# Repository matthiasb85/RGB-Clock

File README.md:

RGB-Clock
=========

RGB-Clock with STM32F1, DCF77, ESP8266, IR RC5 and LDR.

The following features are implemented (1-3) or will be implemented later (4-7)

1.) Fast STM32F103 @72MHz

2.) WS2812B RGB stripe, controlled via PWM & DMA (~0% CPU usage)

3.) DCF77 receiver for time snych

4.) ESP8266 Wifi module for HTTP interface and NTP time synch

5.) IR RC5 receiver integration

6.) Ambient dependent lighting with LDR

7.) MicroSD Card as storage device

The board uses a standard ARM JTAG interface. In addition all remaining GPIOs and the ESP8266 are available on an external pinheader.

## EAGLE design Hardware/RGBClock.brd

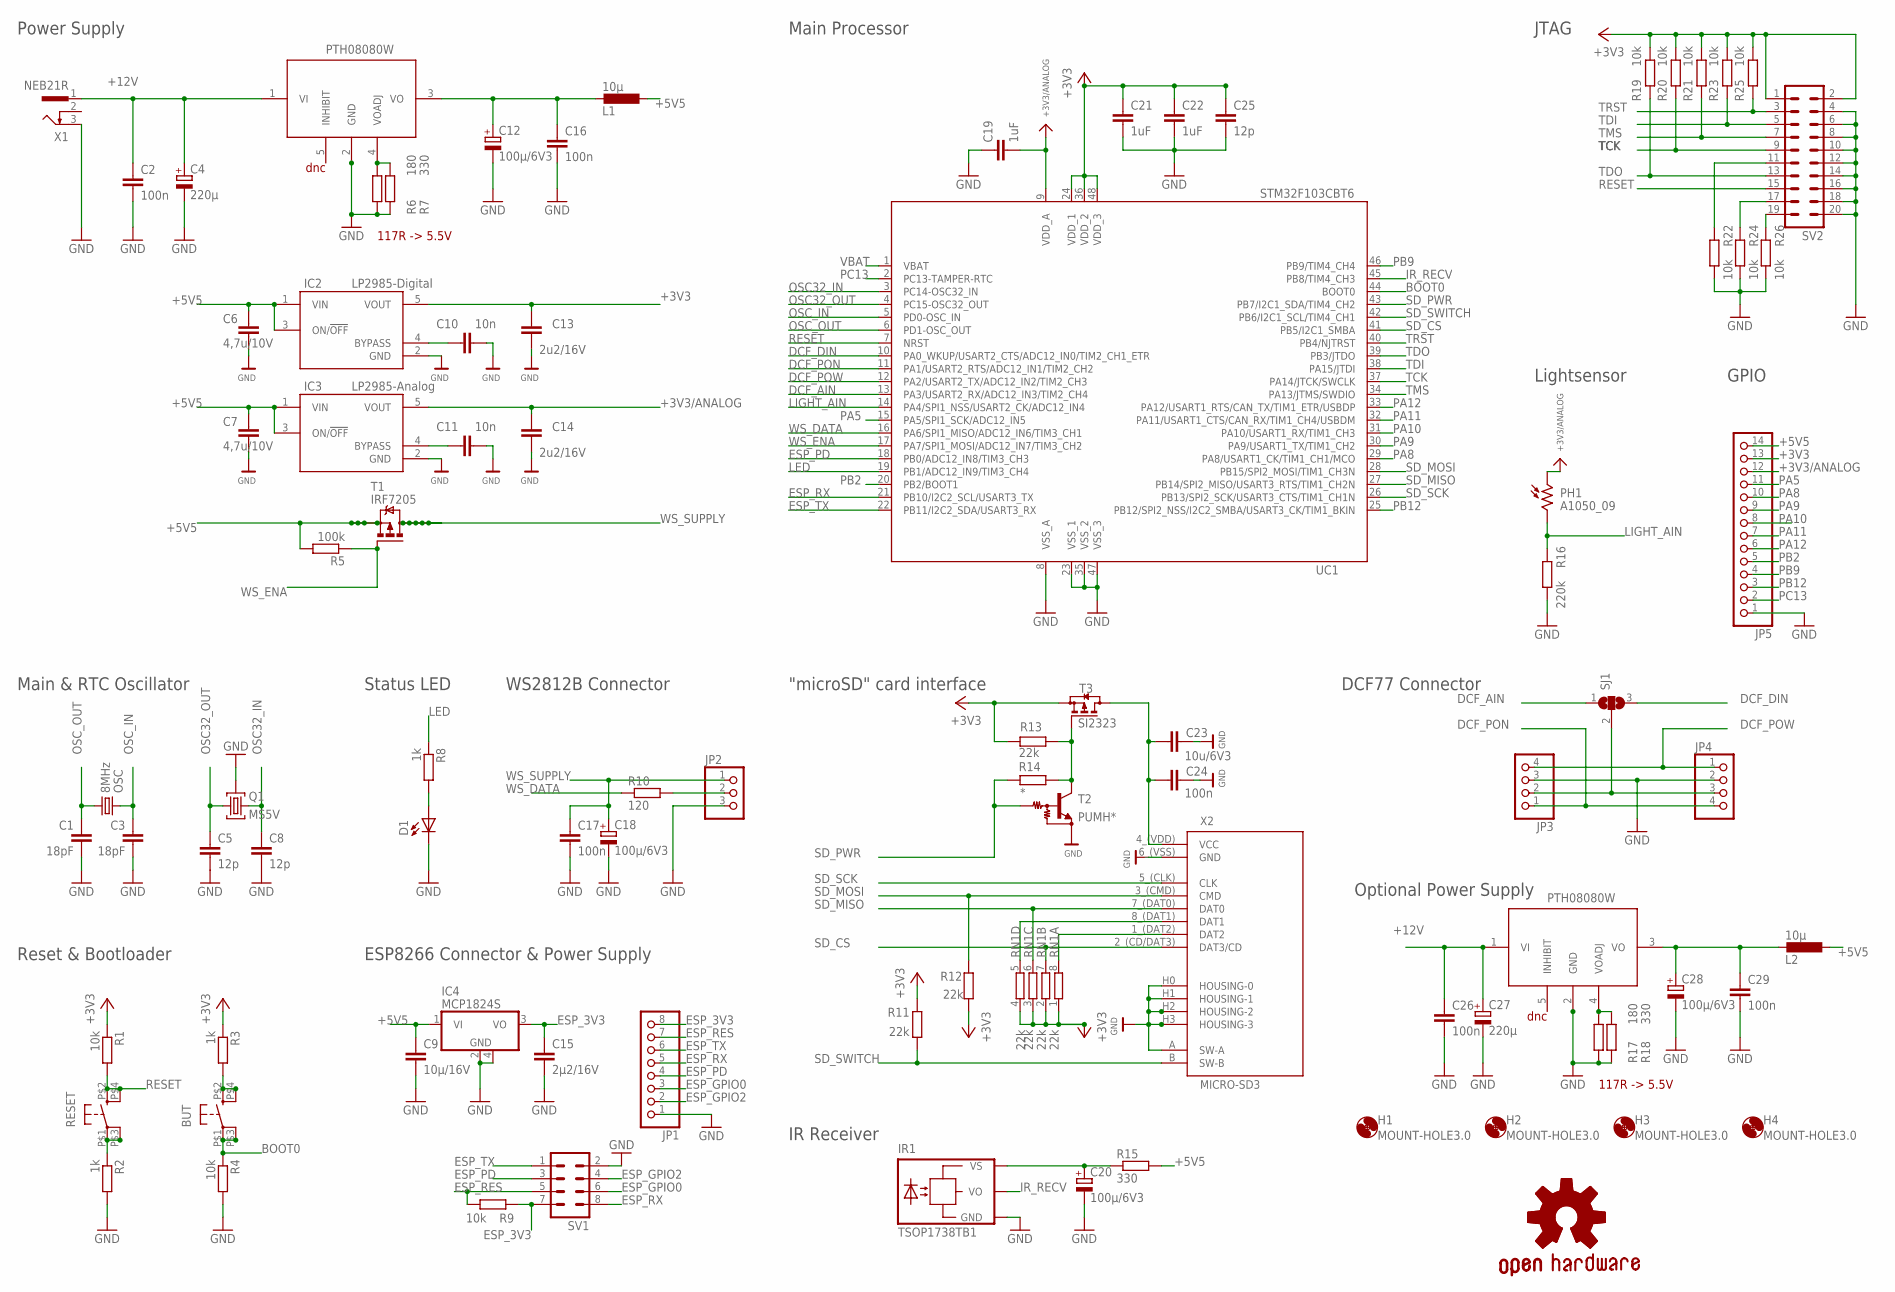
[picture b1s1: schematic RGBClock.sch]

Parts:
BUT: KMR211GLFS; PUSHBUTTON-KMR241GLFS
C1, C3: 18pF; C0402
C2, C16, C17, C26, C29: 100n; C0603
C4, C27: 220µ; E3,5-8
C5, C8, C25: 12p; C0603
C6, C7: 4,7u/10V; C0603-DASHES
C9: 10µ/16V; C0805
C10, C11: 10n; C0603-DASHES
C12, C18, C20, C28: 100µ/6V3; PANASONIC_C
C13, C14: 2u2/16V; C0603-DASHES
C15: 2µ2/16V; C0603
C19, C21, C22: 1uF; C0603
C23: 10u/6V3; C0603-DASHES
C24: 100n; C0603-DASHES
D1: Blue; LED-1206
GOLD_ORB_SM1: OSHWLOGO_GOLD_ORB_MED; OSHW1
H1, H2, H3, H4: MOUNT-HOLE3.0; 3,0
IC1, IC5: PTH08080W
IC2: LP2985-Digital; SOT23-5
IC3: LP2985-Analog; SOT23-5
IC4: MCP1824S; SOT223
IR1: TSOP1738TB1; TSOP17_TB1
JP1: PINHD-1X8/90; 1X08/90
JP2: PINHD-1X3/90; 1X03/90
JP3, JP4: PINHD-1X4; 1X04
JP5: PINHD-1X14/90; 1X14/90
L1, L2: 10µ; SD53-XXX-R; DIGIKEY-PN 513-1457-1-ND
OSC: 8MHz; CRYSTAL-SMD-5X3
PH1: A1050_09; T0-46-A10XX
Q1: MS5V
R1, R4, R9, R19, R20, R21, R22, R23, R24, R25, R26: 10k; R0603
R2, R3, R8: 1k; R0603
R5: 100k; R0603
R6, R17: 180; R0603
R7, R15, R18: 330; R0603
R10: 120; R0603
R11, R12, R13: 22k; R0603-DASHES
R14: *; R0603-DASHES
R16: 220k; R0603
RESET: KMR211GLFS; PUSHBUTTON-KMR241GLFS
RN1: 22k; CRA3A4E; PART_TYPE EXB-N8V
SJ1: SJ2W0603; JUM0603
SV1: MA04-2
SV2: ML20L
T1: IRF7205; SO-08
T2: PUMH*; SOT23
T3: SI2323; SOT23
UC1: STM32F103CBT6; LQFP48
X1: NEB21R
X2: MICRO-SD3; HIROSE_DM3AT

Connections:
+3V3: C13.1, C21.1, C22.1, C25.1, IC2.5 (VOUT), JP5.13, R1.1, R3.1, R11.2, R12.2, R13.2, R19.1, R20.1, R21.1, R23.1, R25.1, RN1.1, RN1.2 (1), RN1.3 (1), RN1.4 (1), SV2.1, SV2.2, T3.2 (S), UC1.24 (VDD_1), UC1.36 (VDD_2), UC1.48 (VDD_3)
+3V3/ANALOG: C14.1, C19.2, IC3.5 (VOUT), JP5.12, PH1.1, UC1.9 (VDD_A)
+5V5: C6.1, C7.1, C9.1, IC2.1 (VIN), IC2.3 (ON/!OFF), IC3.1 (VIN), IC3.3 (ON/!OFF), IC4.1 (VI), JP5.14, L1.1, L2.1, R5.2, R15.2, T1.1 (S), T1.2 (S), T1.3 (S)
+6V_EXT: C12.+, C16.1, IC1.3 (VO), L1.2
+6V_EXT1: C28.+, C29.1, IC5.3 (VO), L2.2
+12V: C2.1, C4.+, C26.1, C27.+, IC1.1 (VI), IC5.1 (VI), X1.1
BOOT0: BUT.P$1 (1), BUT.P$3 (3), R4.1, UC1.44 (BOOT0)
DCF_AIN: SJ1.1, UC1.13 (PA3/USART2_RX/ADC12_IN3/TIM2_CH4)
DCF_DIN: SJ1.3, UC1.10 (PA0_WKUP/USART2_CTS/ADC12_IN0/TIM2_CH1_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)
DCF_PON: JP3.1, JP4.4, UC1.11 (PA1/USART2_RTS/ADC12_IN1/TIM2_CH2)
DCF_POW: JP3.4, JP4.1, UC1.12 (PA2/USART2_TX/ADC12_IN2/TIM2_CH3)
ESP_3V3: C15.1, IC4.3 (VO), JP1.8, R9.2, SV1.7
ESP_GPIO0: JP1.3, SV1.6
ESP_GPIO2: JP1.2, SV1.4
ESP_PD: JP1.4, SV1.3, UC1.18 (PB0/ADC12_IN8/TIM3_CH3)
ESP_RES: JP1.7, R9.1, SV1.5
ESP_RX: JP1.5, SV1.8, UC1.21 (PB10/I2C2_SCL/USART3_TX)
ESP_TX: JP1.6, SV1.1, UC1.22 (PB11/I2C2_SDA/USART3_RX)
GND: C1.2, C2.2, C3.2, C4.-, C5.2, C6.2, C7.2, C8.2, C9.2, C10.2, C11.2, C12.-, C13.2, C14.2, C15.2, C16.2, C17.2, C18.-, C19.1, C20.-, C21.2, C22.2, C23.2, C24.2, C25.2, C26.2, C27.-, C28.-, C29.2, D1.C, IC1.2 (GND), IC2.2 (GND), IC3.2 (GND), IC4.2 (GND), IC4.4 (GND), IC5.2 (GND), IR1.GND, JP1.1, JP2.3, JP3.3, JP4.2, JP5.1, Q1.H (3), R2.2, R4.2, R6.2, R7.2, R16.1, R17.2, R18.2, R22.1, R24.1, R26.1, SV1.2, SV2.4, SV2.6, SV2.8, SV2.10, SV2.12, SV2.14, SV2.16, SV2.18, SV2.20, T2.2 (E), UC1.8 (VSS_A), UC1.23 (VSS_1), UC1.35 (VSS_2), UC1.47 (VSS_3), X1.3, X2.6_(VSS) (GND), X2.A (SW-A), X2.H0 (HOUSING-0), X2.H1 (HOUSING-1), X2.H2 (HOUSING-2), X2.H3 (HOUSING-3)
IR_RECV: IR1.VO, UC1.45 (PB8/TIM4_CH3)
LED: R8.1, UC1.19 (PB1/ADC12_IN9/TIM3_CH4)
LIGHT_AIN: PH1.2, R16.2, UC1.14 (PA4/SPI1_NSS/USART2_CK/ADC12_IN4)
LP2985_BYPASS: C11.1, IC3.4 (BYPASS)
LP2985_BYPASS1: C10.1, IC2.4 (BYPASS)
unnamed: BUT.P$2 (2), BUT.P$4 (4), R3.2
unnamed: D1.A, R8.2
unnamed: JP2.2, R10.2
unnamed: R2.1, RESET.P$1 (1), RESET.P$3 (3)
unnamed: IC5.4 (VOADJ), R17.1, R18.1
unnamed: R26.2, SV2.19
unnamed: JP3.2, JP4.3, SJ1.2
unnamed: R24.2, SV2.17
unnamed: R22.2, SV2.11
unnamed: C20.+, IR1.VS, R15.1
unnamed: RN1.8 (2), X2.1_(DAT2) (DAT2)
unnamed: RN1.5 (2), X2.8_(DAT1) (DAT1)
unnamed: IC1.4 (VOADJ), R6.1, R7.1
OSC32_IN: C8.1, Q1.2, UC1.3 (PC14-OSC32_IN)
OSC32_OUT: C5.1, Q1.1, UC1.4 (PC15-OSC32_OUT)
OSC_IN: C3.1, OSC.3 (2), UC1.5 (PD0-OSC_IN)
OSC_OUT: C1.1, OSC.1, UC1.6 (PD1-OSC_OUT)
PA5: JP5.11, UC1.15 (PA5/SPI1_SCK/ADC12_IN5)
PA8: JP5.10, UC1.29 (PA8/USART1_CK/TIM1_CH1/MCO)
PA9: JP5.9, UC1.30 (PA9/USART1_TX/TIM1_CH2)
PA10: JP5.8, UC1.31 (PA10/USART1_RX/TIM1_CH3)
PA11: JP5.7, UC1.32 (PA11/USART1_CTS/CAN_RX/TIM1_CH4/USBDM)
PA12: JP5.6, UC1.33 (PA12/USART1_RTS/CAN_TX/TIM1_ETR/USBDP)
PB2: JP5.5, UC1.20 (PB2/BOOT1)
PB9: JP5.4, UC1.46 (PB9/TIM4_CH4)
PB12: JP5.3, UC1.25 (PB12/SPI2_NSS/I2C2_SMBA/USART3_CK/TIM1_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)
PC13: JP5.2, UC1.2 (PC13-TAMPER-RTC)
RESET: R1.2, RESET.P$2 (2), RESET.P$4 (4), SV2.15, UC1.7 (NRST)
SDIO_VCC: C23.1, C24.1, T3.3 (D), X2.4_(VDD) (VCC)
SD_CS: RN1.7 (2), UC1.41 (PB5/I2C1_SMBA), X2.2_(CD/DAT3) (DAT3/CD)
SD_MISO: RN1.6 (2), UC1.27 (PB14/SPI2_MISO/USART3_RTS/TIM1_CH2N), X2.7_(DAT0) (DAT0)
SD_MOSI: R12.1, UC1.28 (PB15/SPI2_MOSI/TIM1_CH3N), X2.3_(CMD) (CMD)
SD_PWR: R14.2, T2.1 (B), UC1.43 (PB7/I2C1_SDA/TIM4_CH2)
SD_PWR_INV: R13.1, R14.1, T2.3 (C), T3.1 (G)
SD_SCK: UC1.26 (PB13/SPI2_SCK/USART3_CTS/TIM1_CH1N), X2.5_(CLK) (CLK)
SD_SWITCH: R11.1, UC1.42 (PB6/I2C1_SCL/TIM4_CH1), X2.B (SW-B)
TCK: R20.2, SV2.9, UC1.37 (PA14/JTCK/SWCLK)
TDI: R23.2, SV2.5, UC1.38 (PA15/JTDI)
TDO: R19.2, SV2.13, UC1.39 (PB3/JTDO)
TMS: R21.2, SV2.7, UC1.34 (PA13/JTMS/SWDIO)
TRST: R25.2, SV2.3, UC1.40 (PB4/NJTRST)
VBAT: UC1.1 (VBAT)
WS_DATA: R10.1, UC1.16 (PA6/SPI1_MISO/ADC12_IN6/TIM3_CH1)
WS_ENA: R5.1, T1.4 (G), UC1.17 (PA7/SPI1_MOSI/ADC12_IN7/TIM3_CH2)
WS_SUPPLY: C17.1, C18.+, JP2.1, T1.5 (D), T1.6 (D), T1.7 (D), T1.8 (D)

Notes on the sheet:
PTH08080W
117R -> 5.5V
dnc
"microSD" card interface
Power Supply
Main Processor
Main & RTC Oscillator
Reset & Bootloader
DCF77 Connector
Status LED
WS2812B Connector
IR Receiver
ESP8266 Connector & Power Supply
JTAG
Lightsensor
GPIO
Optional Power Supply

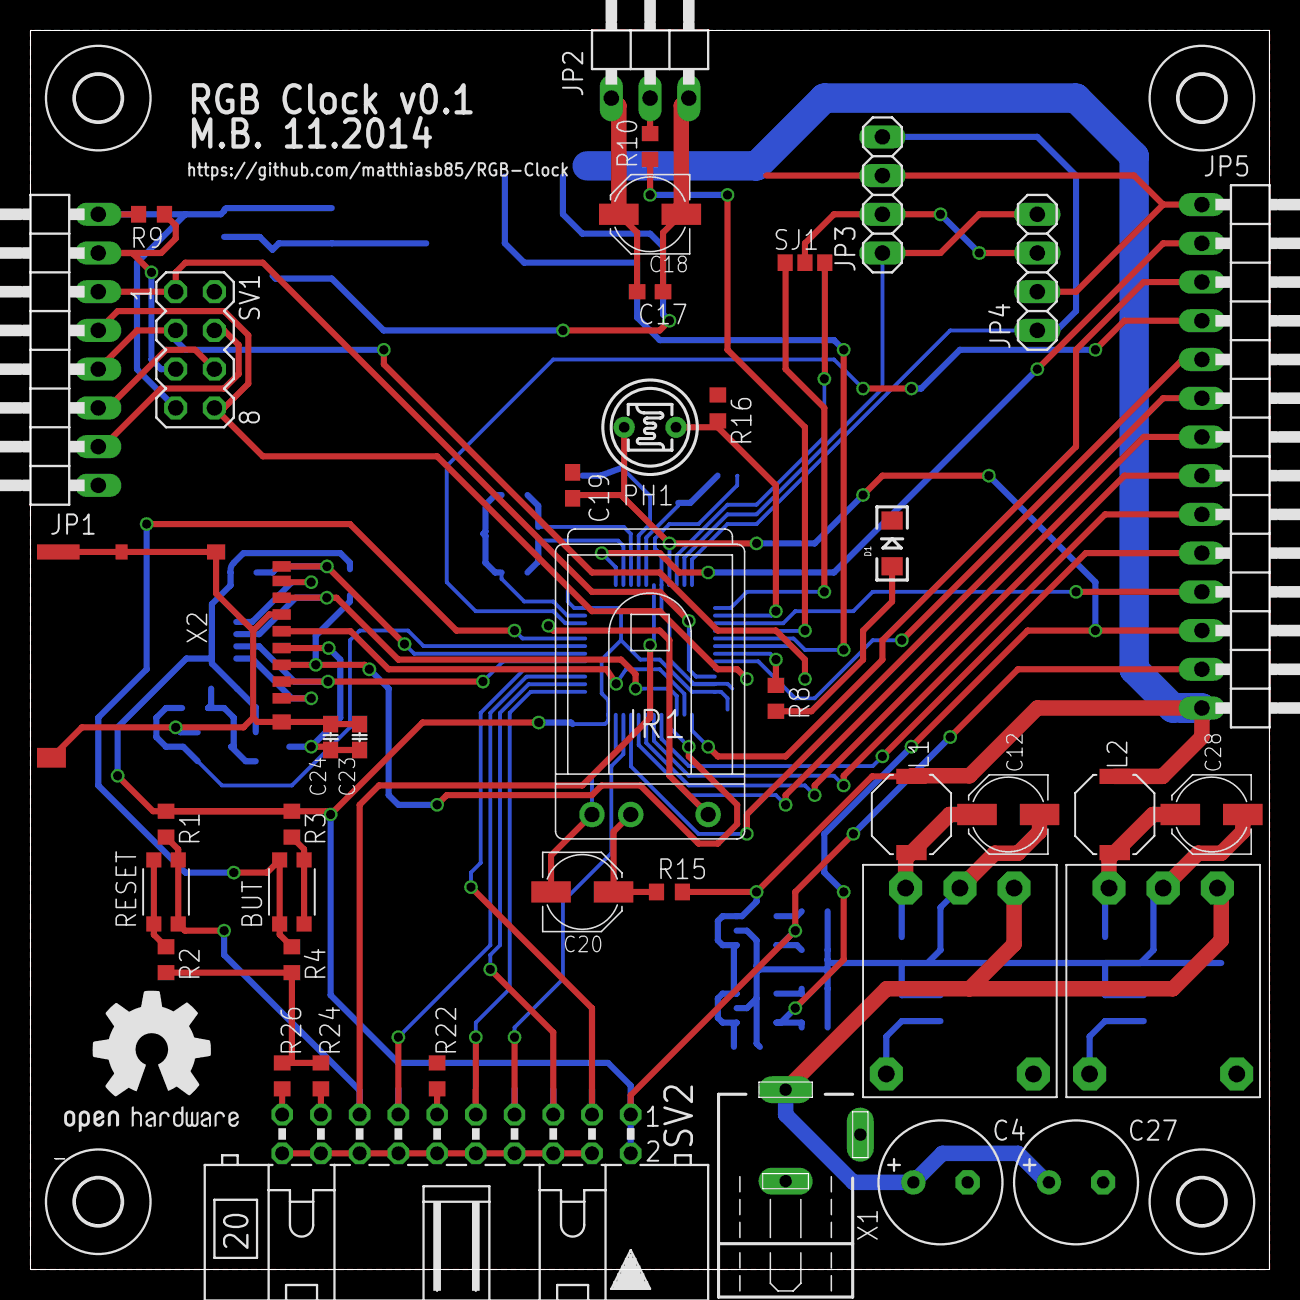
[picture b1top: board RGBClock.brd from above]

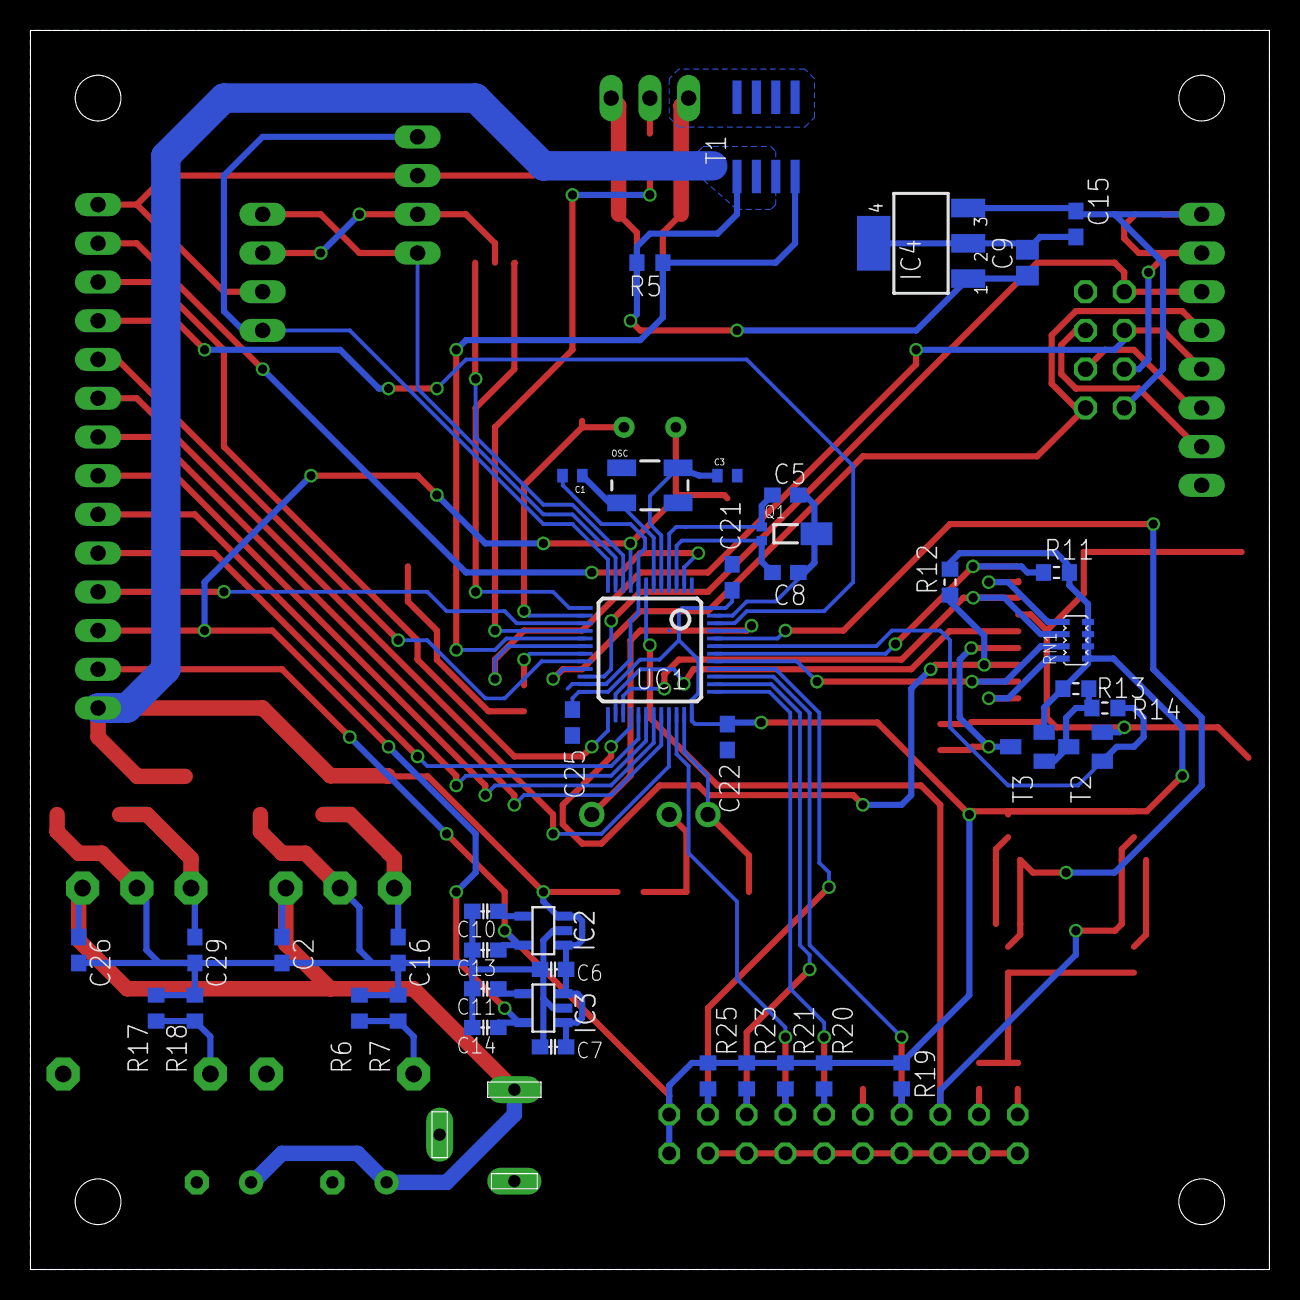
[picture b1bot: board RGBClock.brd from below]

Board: 2 copper layers, 81.3 x 81.3 mm, 89 parts (43 on the bottom side), 68 nets.

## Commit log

2014-11-11 added first version of PCB added frontpanel
2014-11-11 Update README.md
    added line breaks
2014-11-11 added github url on PCB
2014-11-11 some additional information
2014-11-12 fixed typo
2014-11-15 worked on board worked on silkscreen -> first version should be ready within a few commits
2014-11-16 minor changes on board and schematic
2014-11-16 modified board, better placement for C21,22,25
2014-11-16 minor changes on silkscreen
